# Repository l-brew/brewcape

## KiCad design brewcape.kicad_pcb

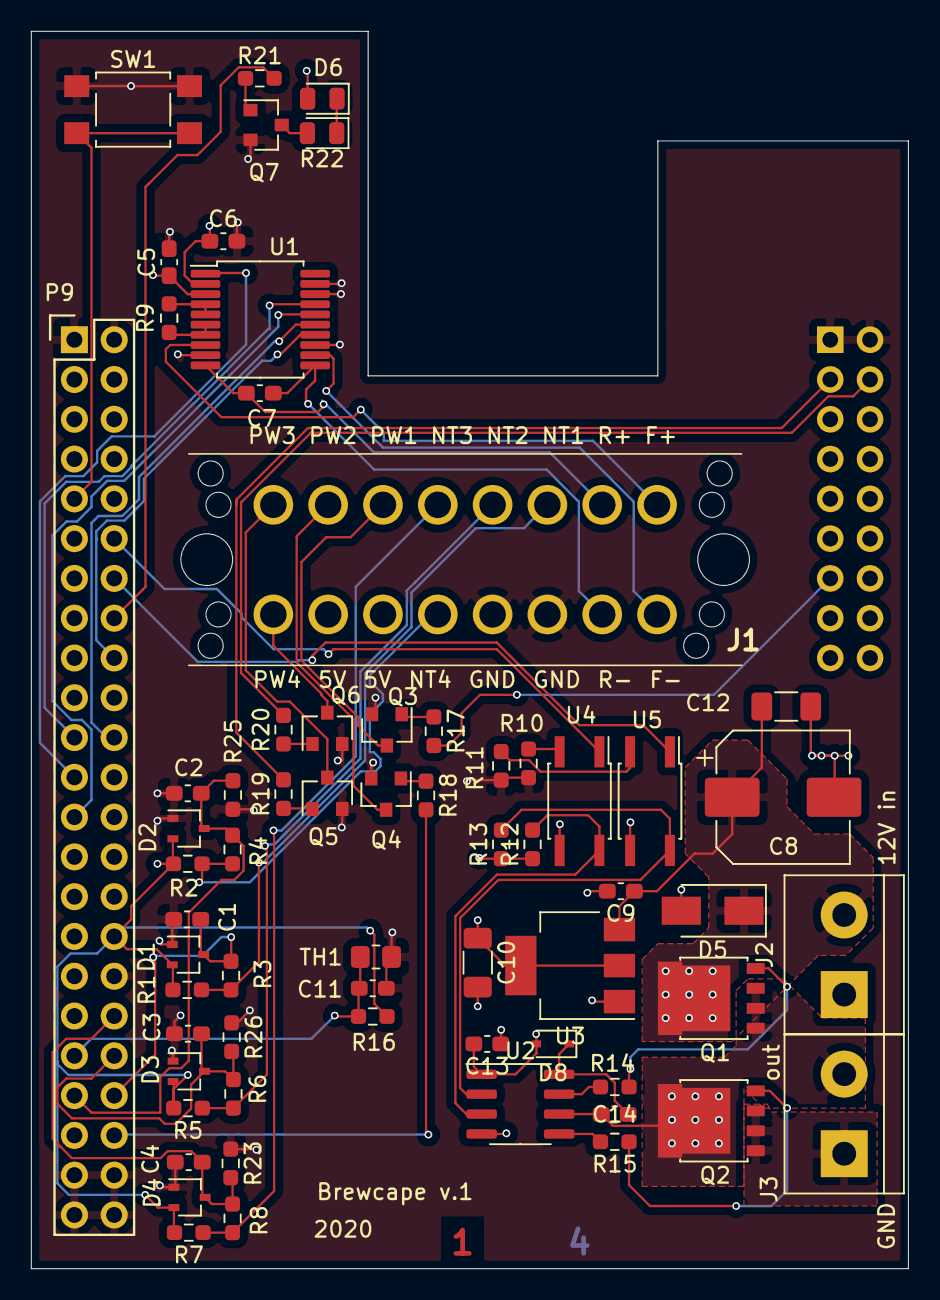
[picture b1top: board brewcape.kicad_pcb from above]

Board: 4 copper layers, 56.0 x 79.0 mm, 65 parts (1 on the bottom side), 57 nets.

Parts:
C1, C2, C3, C4, C11: 10n; C_0603_1608Metric_Pad1.08x0.95mm_HandSolder
C5, C6, C7, C9, C13: 100n; C_0603_1608Metric_Pad1.08x0.95mm_HandSolder
C8: EMZR250ARA471MHA0G; CP_Elec_8x10
C10, C12: C1206C106K4RACTU; C_1206_3216Metric_Pad1.33x1.80mm_HandSolder
C14: 22n; C_0603_1608Metric_Pad1.08x0.95mm_HandSolder
D1, D2, D3, D4: BAT54SW; SOT-323_SC-70
D5: RBR5L30BDD; D_SMA
D6: LED; LED_0805_2012Metric
D8: BAS321,115; D_SOD-323
J1: 1848707
J2, J3: Screw_Terminal_01x02; TerminalBlock_bornier-2_P5.08mm
P8: Conn_02x09_Odd_Even; PinSocket_2x09_P2.54mm_Vertical
P9: BeagleBone_Black_Header; Socket_BeagleBone_Black
Q1, Q2: PSMN9R1-30YL; LFPAK56
Q3, Q4, Q5, Q6, Q7: DMN3730U; SOT-23
R1, R2, R5, R7, R16: 50k; R_0603_1608Metric_Pad0.98x0.95mm_HandSolder
R3, R4, R6, R8: 10k; R_0603_1608Metric_Pad0.98x0.95mm_HandSolder
R9: 400 0.1%; R_0603_1608Metric_Pad0.98x0.95mm_HandSolder
R10, R11, R17, R18, R19, R20, R21: 100; R_0603_1608Metric_Pad0.98x0.95mm_HandSolder
R12, R13: 4.7k; R_0603_1608Metric_Pad0.98x0.95mm_HandSolder
R14, R15: 50; R_0603_1608Metric_Pad0.98x0.95mm_HandSolder
R22: 220; LED_0805_2012Metric
R23, R25, R26: n.c.; R_0603_1608Metric_Pad0.98x0.95mm_HandSolder
SW1: SW_Push; SW_SPST_TL3305A
TH1: NTCG204CH104JTDS; R_0805_2012Metric_Pad1.20x1.40mm_HandSolder
U1: MAX31865xAP; SSOP-20_5.3x7.2mm_P0.65mm
U2: IRS2008S; SOIC-8_3.9x4.9mm_P1.27mm
U3: LD1117S50TR_SOT223; SOT-223-3_TabPin2
U4, U5: LTV-357T; SO-4_4.4x3.6mm_P2.54mm

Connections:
+3V3: C5.1, C6.1, P9.3, P9.4, U1.2, U1.3
+5P: C10.1, C13.2, D8.2, R12.1, R13.1, U2.1, U3.2
+5V: D6.2, J1.6, J1.7, P9.5, P9.6
+12V: C8.1, C9.1, C12.1, D5.1, J2.2, Q1.5, U3.3
ADC1: C1.1, D1.3, P9.40, R3.2
ADC2: C3.1, D3.3, P9.38, R6.2, R26.2
ADC3: C4.1, D4.3, P9.36, R8.2, R23.2
ADC4: C2.1, D2.3, P9.39, R4.2, R25.2
G1: P8.13, R17.2
G2: P9.42, R18.2
G3: P8.3, R19.2
G4: P8.4, R20.2
GND: C1.2, C2.2, C3.2, C4.2, C5.2, C6.2, C11.2, D1.1, D2.1, D3.1, D4.1, J1.3, J1.4, P8.1, P8.2, P9.1, P9.2, P9.34, P9.43, P9.44, P9.45, P9.46, Q3.2, Q4.2, Q5.2, Q6.2, Q7.2, R10.2, R11.2, R23.1, R25.1, R26.1, SW1.1, TH1.2, U1.9, U1.13, U1.18, U1.19
GNDPWR: C8.2, C9.2, C10.2, C12.2, C13.1, D5.2, J2.1, J3.1, Q2.1, Q2.2, Q2.3, U2.4, U3.1, U4.3, U5.3
M_PWM: P9.14, U5.1
M_SD: P9.12, U4.1
NTC1: J1.11, R1.1, R3.1
NTC2: J1.12, R5.1, R6.1
NTC3: J1.13, R7.1, R8.1
NTC4: J1.5, R2.1, R4.1
NTC5: C11.1, P9.37, R16.1, TH1.1
unnamed: C14.1, J3.2, Q1.1, Q1.2, Q1.3, Q2.5, U2.6
unnamed: C14.2, D8.1, U2.8
unnamed: D6.1, R22.1
unnamed: J1.8, Q6.3
unnamed: J1.14, Q3.3
unnamed: J1.15, Q4.3
unnamed: J1.16, Q5.3
unnamed: Q1.4, R14.1
unnamed: Q2.4, R15.1
unnamed: Q3.1, R17.1
unnamed: Q4.1, R18.1
unnamed: Q5.1, R19.1
unnamed: Q6.1, R20.1
unnamed: Q7.1, R21.1
unnamed: Q7.3, R22.2
unnamed: R9.1, U1.4, U1.5
unnamed: R9.2, U1.6, U1.7
unnamed: R10.1, U4.2
unnamed: R11.1, U5.2
unnamed: R12.2, U2.3, U4.4
unnamed: R13.2, U2.2, U5.4
unnamed: R14.2, U2.7
unnamed: R15.2, U2.5
PT_CS: P9.25, U1.16
PT_DRDY: P9.23, U1.1
PT_F+: J1.9, U1.8
PT_F-: J1.1, U1.12
PT_R+: C7.1, J1.10, U1.10
PT_R-: C7.2, J1.2, U1.11
PT_SCLK: P9.22, U1.15
PT_SDI: P9.18, U1.14
PT_SDO: P9.21, U1.17
PWR_BUT: P9.9, SW1.2
SYS_5V: P9.7, P9.8
VDD_ADC: D1.2, D2.2, D3.2, D4.2, P9.32, R1.2, R2.2, R5.2, R7.2, R16.2
led: P9.16, R21.2

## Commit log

2021-08-18 changed optocouplers
